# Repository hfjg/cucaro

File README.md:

CuCaRo is a **Cu**riosity Inspired **Ca**mera **Ro**ver, roughly adopting the shape, chassis and drive/steer mechanisms.

# Overview
CuCaRo is built of following modules:
(For more details please refer to the module documentation).
1. [Body](./Modules/01_Body/Documents/01_Body_README.md)
2. BatMan (The Battery Manager)
3. DriSu (Drive and STeering units, six in total)
3. ACOS (Anti Collision Sensors)
4. RunCam

Modules communicate with each other via CAN-Bus.

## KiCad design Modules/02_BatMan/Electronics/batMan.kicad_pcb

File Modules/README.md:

CuCaRo is a **Cu**riosity Inspired **Ca**mera **Ro**ver, roughly adopting the shape, chassis and drive/steer mechanisms.

# Overview
CuCaRo is built of following modules:
(For more details please refer to the module documentation).
1. [Body](./Modules/01_Body/Documents/01_Body_README.md)
2. [BatMan](./Modules/02_BatMan/Documents/02_BatMan_README.md) (The Battery Manager)
3. DriSu (Drive and STeering units, six in total)
3. ACOS (Anti Collision Sensors)
4. RunCam

Modules communicate with each other via CAN-Bus.

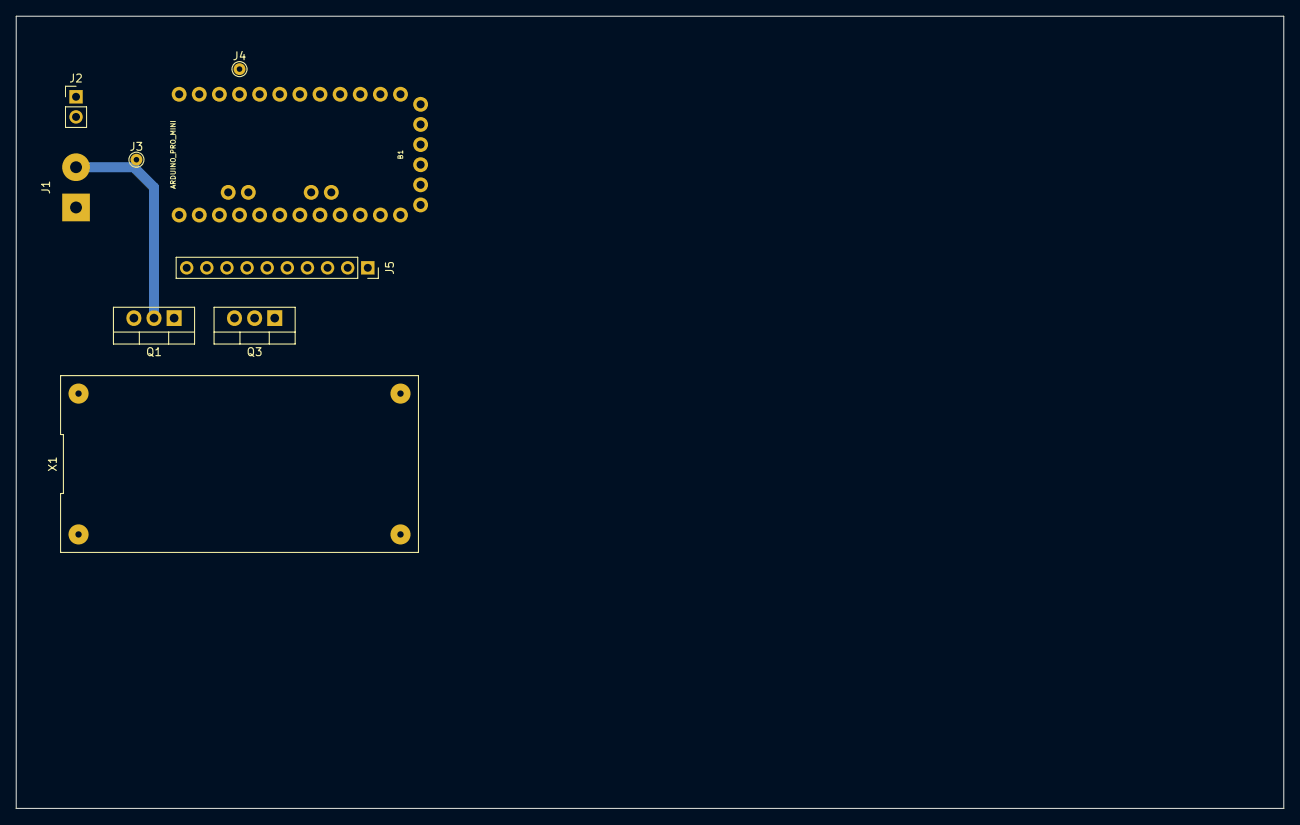
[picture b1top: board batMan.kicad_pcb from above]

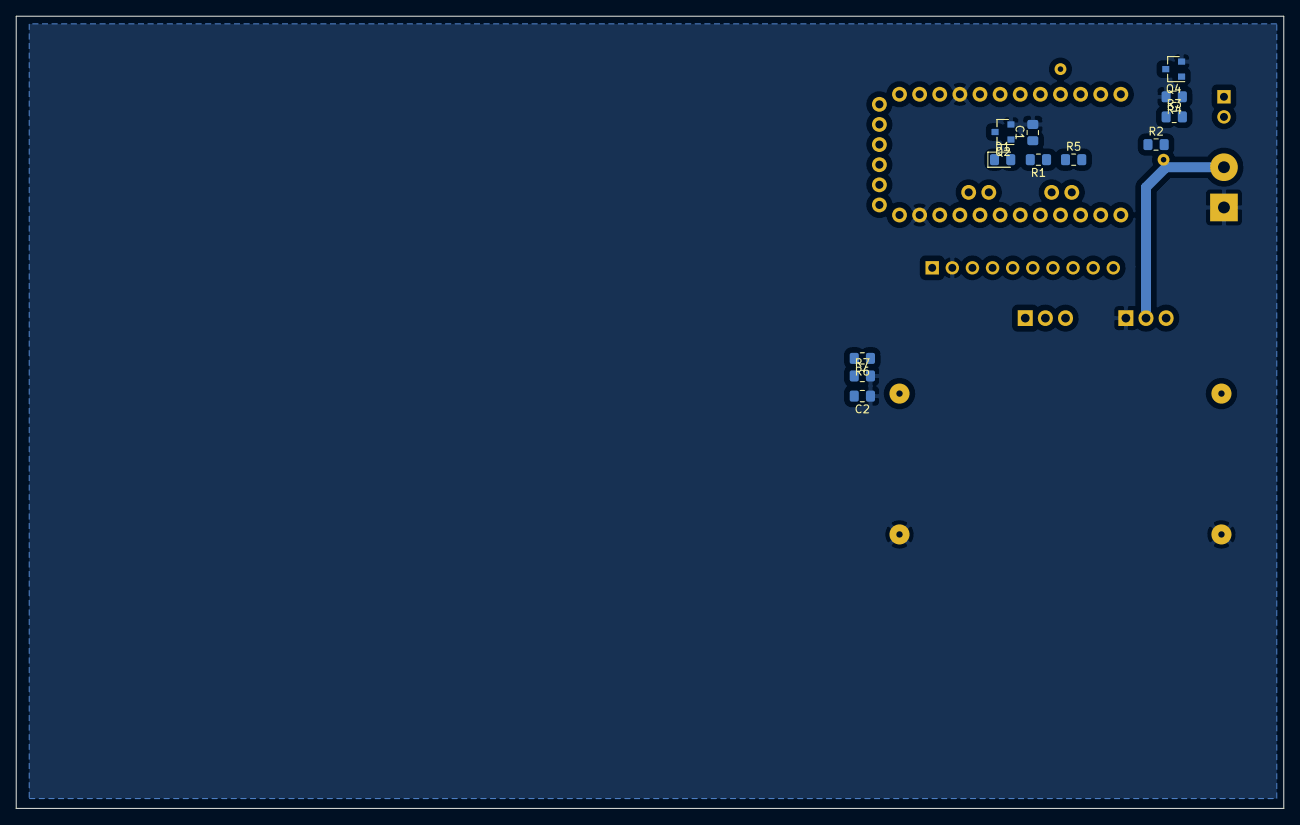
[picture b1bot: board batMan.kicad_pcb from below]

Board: 2 copper layers, 160.0 x 100.0 mm, 21 parts (12 on the bottom side), 16 nets.

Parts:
B1: ARDUINO_PRO_MINI
C1, C2: 100n; C_0805_2012Metric_Pad1.15x1.40mm_HandSolder
D1: LED; LED_0805_2012Metric_Pad1.15x1.40mm_HandSolder
J1: PWR_IN; SolderWirePad_1x02_P5.08mm_Drill1.5mm
J2: BUT,TON; PinHeader_1x02_P2.54mm_Vertical
J3: TP2; TestPoint_THTPad_D1.5mm_Drill0.7mm
J4: TP1; TestPoint_THTPad_D1.5mm_Drill0.7mm
J5: ADS1115; PinSocket_1x10_P2.54mm_Vertical
Q1, Q3: IRF5305; TO-220-3_Vertical
Q2, Q4: BC847; SOT-23
R1, R3, R4, R5, R6, R7: 10K; R_0805_2012Metric_Pad1.15x1.40mm_HandSolder
R2: 1K; R_0805_2012Metric_Pad1.15x1.40mm_HandSolder
X1: DCDC_Buck_Module3A; DIP-4_700

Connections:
/A0: C2.2, J5.7, R6.2, R7.1
/BAT+: J1.2, Q1.2
/BUTTON: B1.9, J4.1, Q4.3
/PWR_HOLD: B1.10, J3.1, R5.2
/SCL: B1.A5, J5.3
/SDA: B1.A4, J5.4
/VBAT: Q1.3, Q3.3, R2.1
/VBAT_SW: Q3.2, R6.1, X1.4
GNDPWR: B1.4, B1.23, C1.2, C2.1, J1.1, J5.2, Q1.1, Q2.2, Q4.2, R4.2, R7.2, X1.1, X1.2
unnamed: C1.1, R1.1, R5.1
unnamed: D1.1, Q2.3
unnamed: D1.2, J2.2, R3.2
unnamed: J2.1, Q4.1, R4.1
unnamed: Q2.1, R1.2
unnamed: Q3.1, R2.2, R3.1
VCC: B1.21, J5.1, X1.3

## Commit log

2020-07-02 Add files via upload
    First upload to github
2020-07-02 Add files via upload
    Module Body, Files for differential
2020-07-02 Rename boxLowerShell_x1.stl to Modules/01_Body/boxLowerShell_x1.stl
2020-07-02 reorganized folders
2020-07-02 reorg folders
2020-07-02 further imports
2020-07-05 added .gitignore file
2020-07-10 updated from local repository
2020-07-20 various changes
2020-08-11 united various directories
2020-08-15 collected files, part I
2020-08-15 collected files, part II
2020-08-31 added axis bearing holder
2020-08-31 files collected
2020-09-09 daily update
